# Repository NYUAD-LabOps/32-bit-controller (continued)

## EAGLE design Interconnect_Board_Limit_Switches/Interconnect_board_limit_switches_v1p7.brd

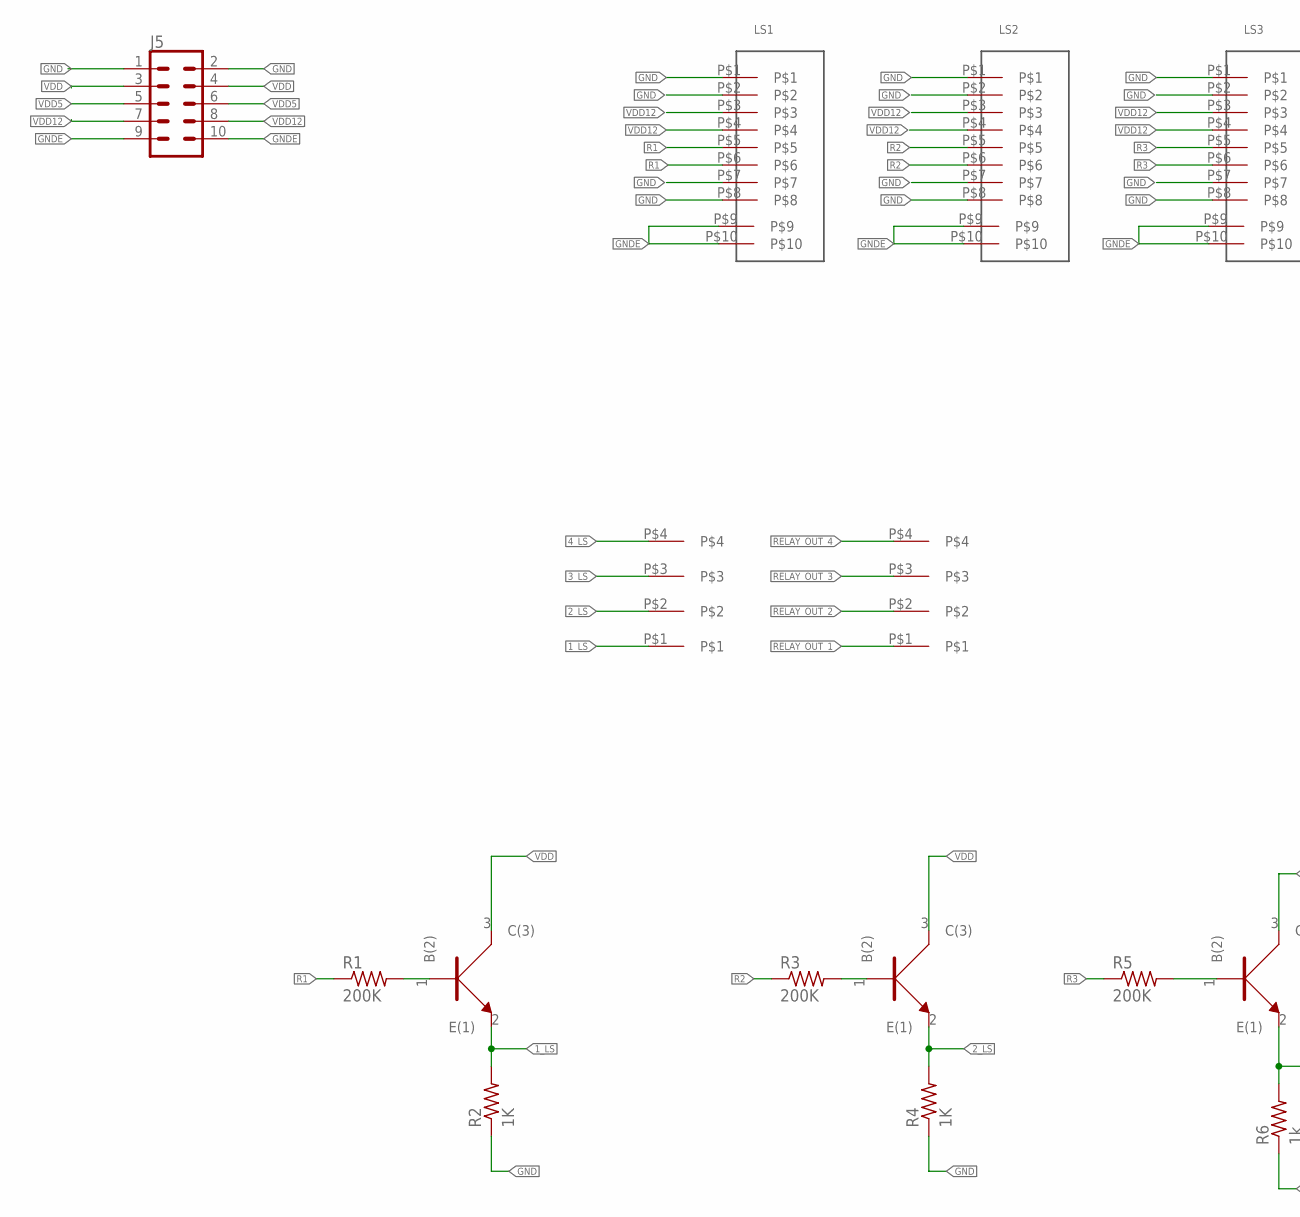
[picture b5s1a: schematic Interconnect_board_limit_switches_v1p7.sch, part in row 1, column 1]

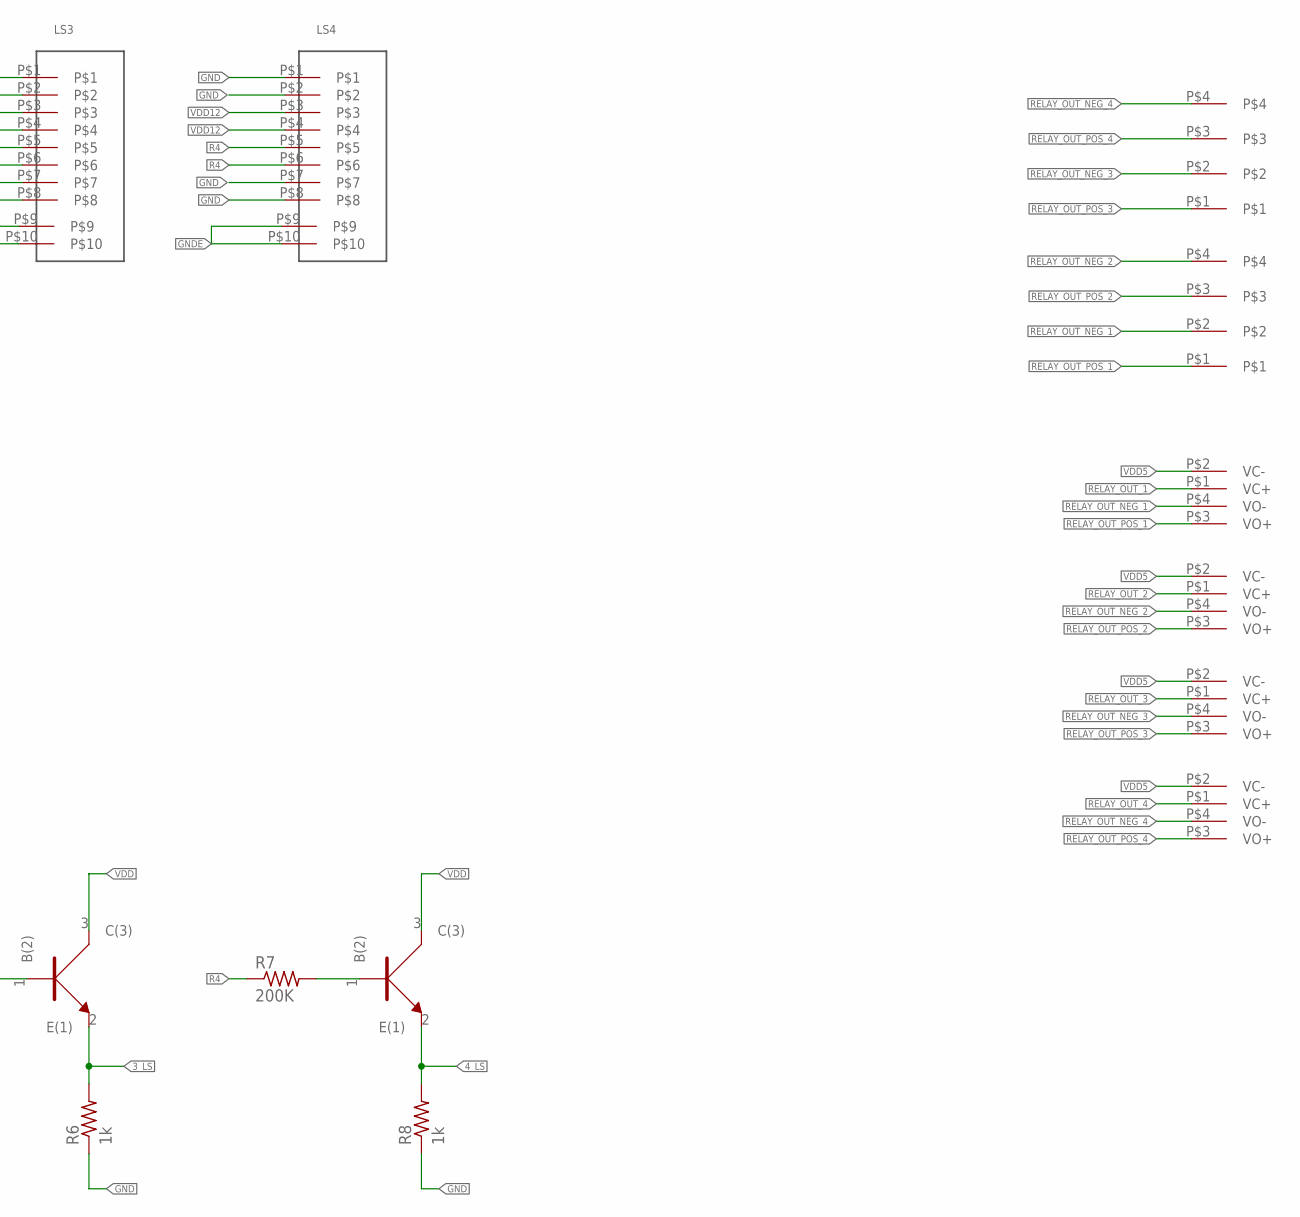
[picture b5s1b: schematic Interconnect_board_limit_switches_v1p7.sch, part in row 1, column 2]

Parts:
J1, J2, J3, J4: 3.81MM_1_X_4_RT_ANGLE_PLUG_HEADER; 1X4_3.81MM_PITCH
J5: CONN_05X2PTH; 2X5
LS1, LS2, LS3, LS4: RJ45_SMTRJ; RJ45_SMT
R1, R3, R5, R7: 200K; 0402
R2, R4: 1K; 0402
R6, R8: 1k; 0402
RELAY_1, RELAY_2, RELAY_4, RELAY_5: RELAY_KYOTO_KF0604D
U1, U2, U3, U4: BC846BW; SOT323

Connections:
1_LS: J4.P$1, R2.P$2 (2), U1.2 (E(1))
2_LS: J4.P$2, R4.P$2 (2), U2.2 (E(1))
3_LS: J4.P$3, R6.P$2 (2), U3.2 (E(1))
4_LS: J4.P$4, R8.P$2 (2), U4.2 (E(1))
GND: J5.1, J5.2, LS1.P$1, LS1.P$2, LS1.P$7, LS1.P$8, LS2.P$1, LS2.P$2, LS2.P$7, LS2.P$8, LS3.P$1, LS3.P$2, LS3.P$7, LS3.P$8, LS4.P$1, LS4.P$2, LS4.P$7, LS4.P$8, R2.P$1 (1), R4.P$1 (1), R6.P$1 (1), R8.P$1 (1)
GNDE: J5.9, J5.10, LS1.P$9, LS1.P$10, LS2.P$9, LS2.P$10, LS3.P$9, LS3.P$10, LS4.P$9, LS4.P$10
unnamed: R1.P$2 (2), U1.1 (B(2))
unnamed: R7.P$2 (2), U4.1 (B(2))
unnamed: R3.P$2 (2), U2.1 (B(2))
unnamed: R5.P$2 (2), U3.1 (B(2))
R1: LS1.P$5, LS1.P$6, R1.P$1 (1)
R2: LS2.P$5, LS2.P$6, R3.P$1 (1)
R3: LS3.P$5, LS3.P$6, R5.P$1 (1)
R4: LS4.P$5, LS4.P$6, R7.P$1 (1)
RELAY_OUT_1: J3.P$1, RELAY_1.P$1 (VC+)
RELAY_OUT_2: J3.P$2, RELAY_2.P$1 (VC+)
RELAY_OUT_3: J3.P$3, RELAY_5.P$1 (VC+)
RELAY_OUT_4: J3.P$4, RELAY_4.P$1 (VC+)
RELAY_OUT_NEG_1: J2.P$2, RELAY_1.P$4 (VO-)
RELAY_OUT_NEG_2: J2.P$4, RELAY_2.P$4 (VO-)
RELAY_OUT_NEG_3: J1.P$2, RELAY_5.P$4 (VO-)
RELAY_OUT_NEG_4: J1.P$4, RELAY_4.P$4 (VO-)
RELAY_OUT_POS_1: J2.P$1, RELAY_1.P$3 (VO+)
RELAY_OUT_POS_2: J2.P$3, RELAY_2.P$3 (VO+)
RELAY_OUT_POS_3: J1.P$1, RELAY_5.P$3 (VO+)
RELAY_OUT_POS_4: J1.P$3, RELAY_4.P$3 (VO+)
VDD: J5.3, J5.4, U1.3 (C(3)), U2.3 (C(3)), U3.3 (C(3)), U4.3 (C(3))
VDD5: J5.5, J5.6, RELAY_1.P$2 (VC-), RELAY_2.P$2 (VC-), RELAY_4.P$2 (VC-), RELAY_5.P$2 (VC-)
VDD12: J5.7, J5.8, LS1.P$3, LS1.P$4, LS2.P$3, LS2.P$4, LS3.P$3, LS3.P$4, LS4.P$3, LS4.P$4

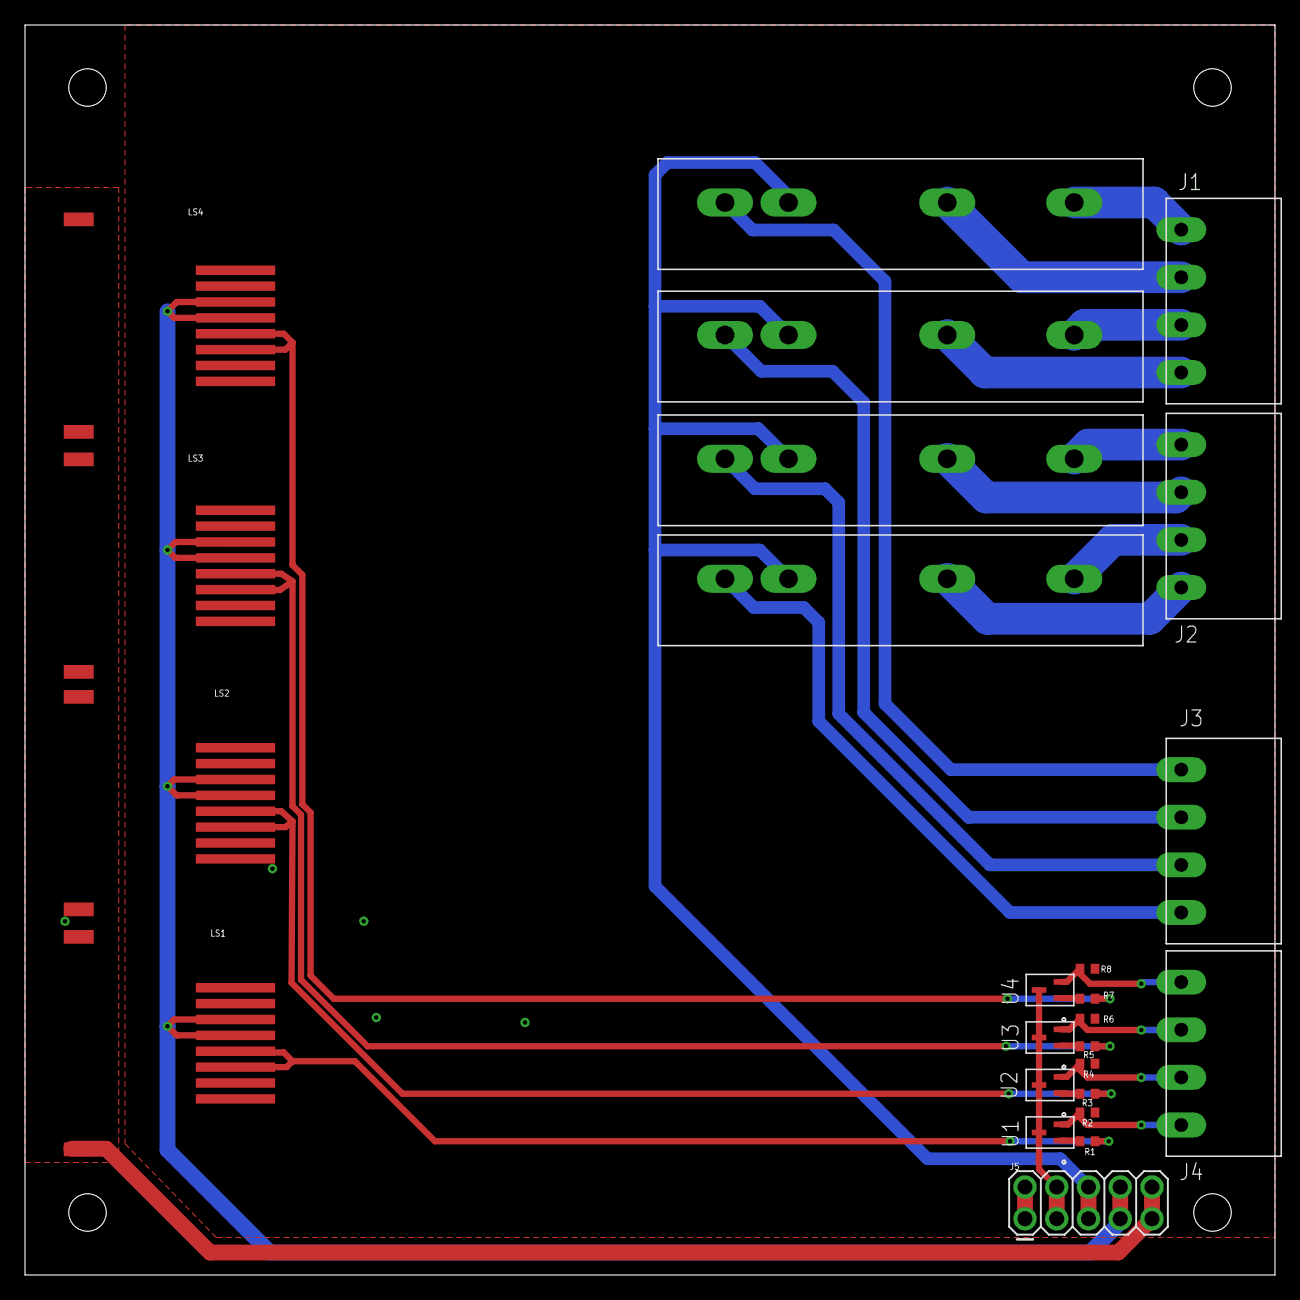
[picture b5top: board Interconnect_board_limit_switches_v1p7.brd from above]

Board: 2 copper layers, 100.0 x 100.0 mm, 25 parts (0 on the bottom side), 29 nets.

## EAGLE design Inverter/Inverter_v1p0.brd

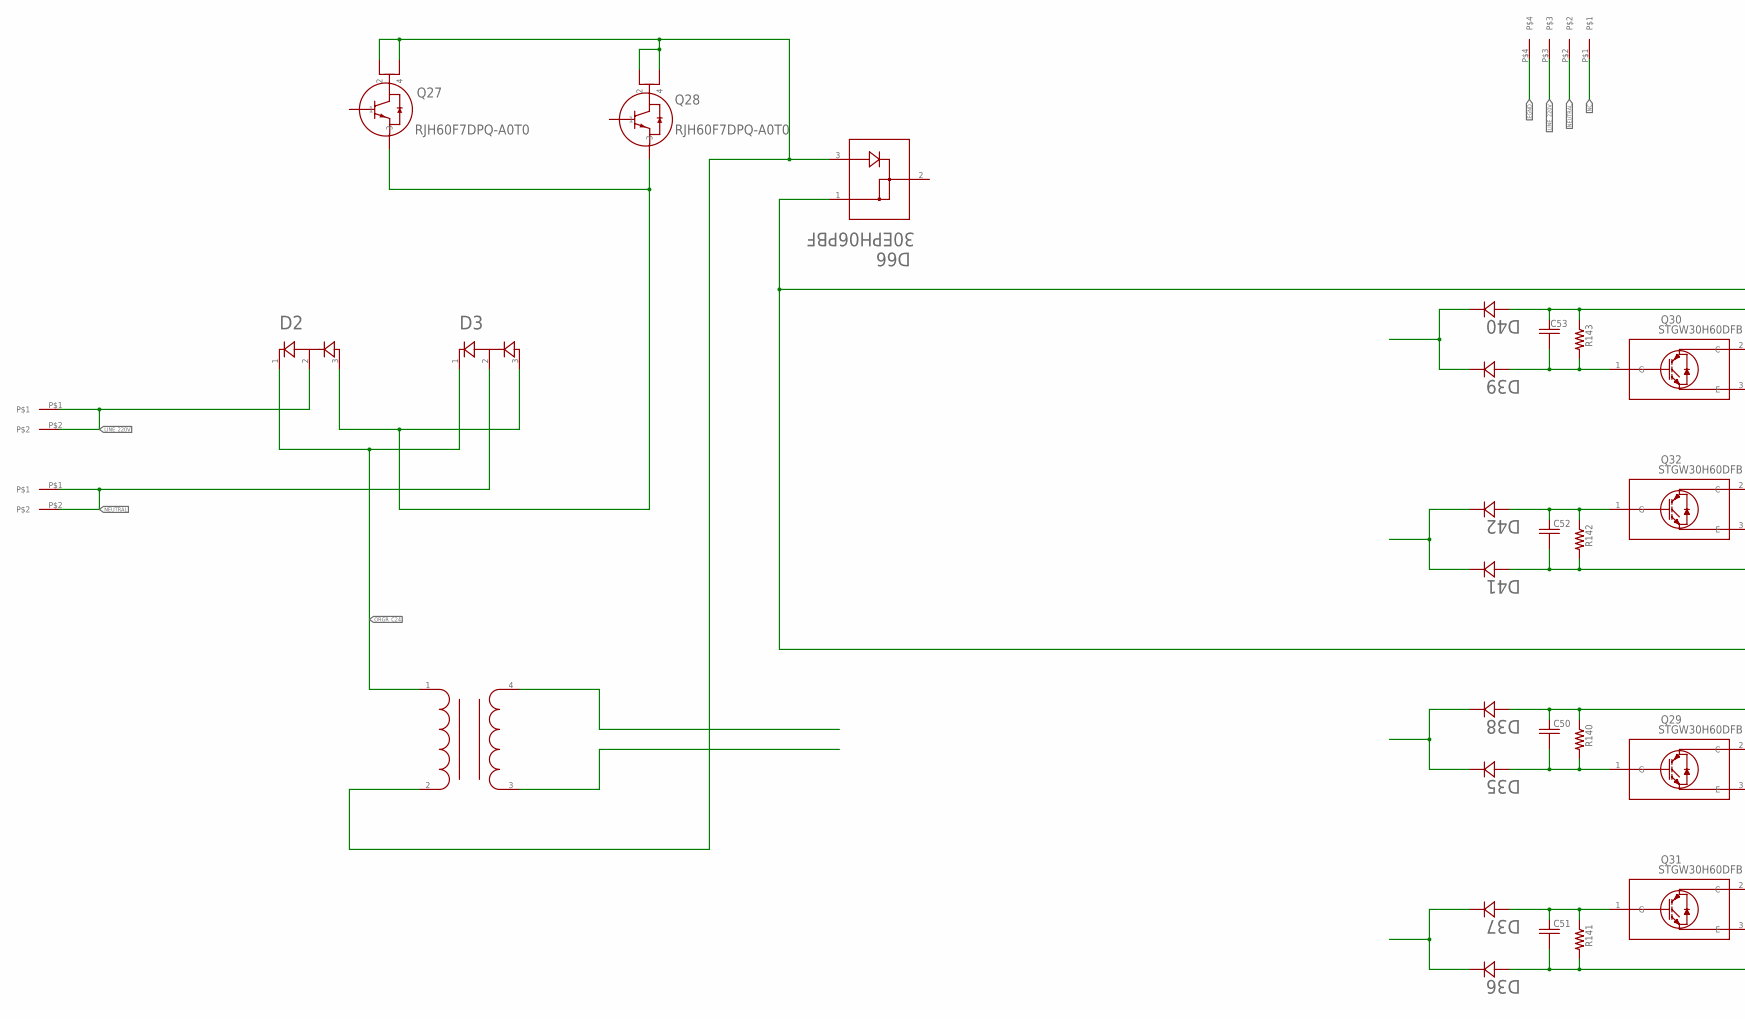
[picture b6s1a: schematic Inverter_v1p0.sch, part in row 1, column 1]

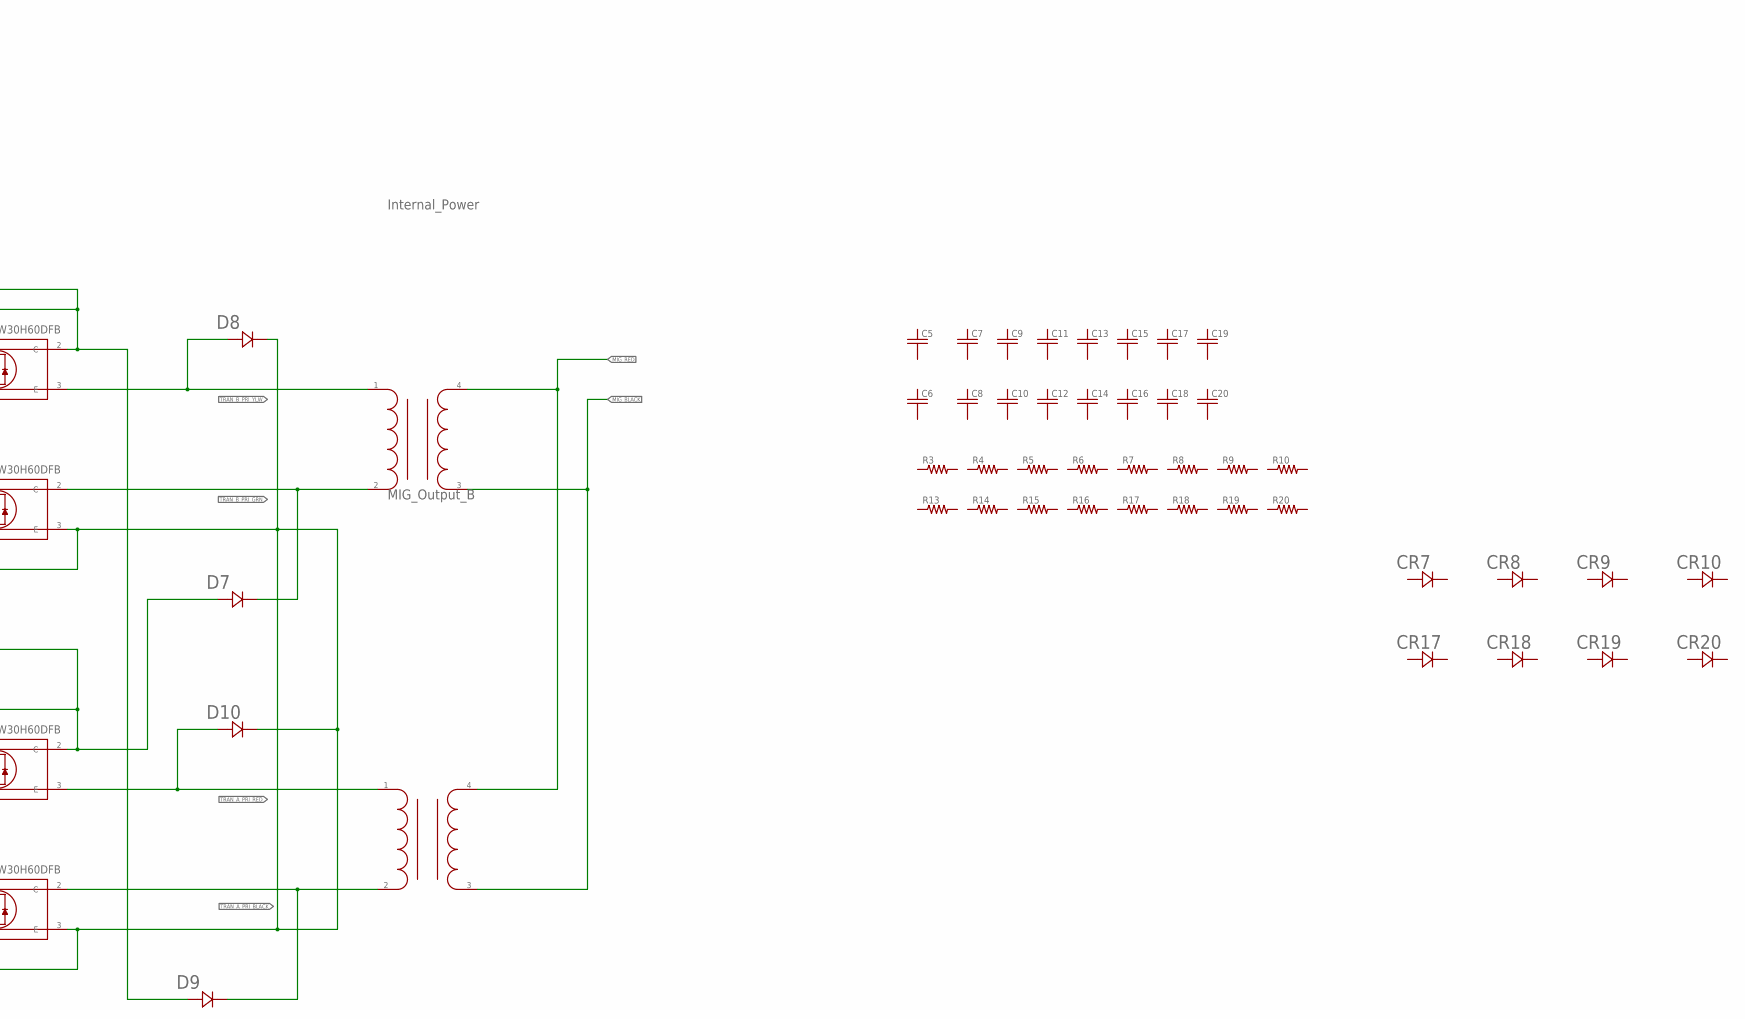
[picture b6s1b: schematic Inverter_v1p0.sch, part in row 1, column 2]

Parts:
C5, C6, C7, C8, C9, C10, C11, C12, C13, C14, C15, C16, C17, C18, C19, C20, C50, C51, C52, C53: C_0805; 0805
CR7, CR8, CR9, CR10, CR17, CR18, CR19, CR20: GF1D-E3; DO-214BA_VIS
D2, D3: SDD25N12; TO-247AD
D7, D8, D9, D10, D35, D36, D37, D38, D39, D40, D41, D42: GF1D-E3; DO-214BA_VIS
D66: 30EPH06PBF; TO-247AC_MOD_VIS
J1: 4-pos; 1X4_3.81MM_PITCH
J2, J3: 2-pos; 2_3.81MM_PITCH
Q27, Q28: RJH60F7DPQ-A0T0; TO-247A_REN
Q29, Q30, Q31, Q32: STGW30H60DFB; TO-247_STM
R3, R4, R5, R6, R7, R8, R9, R10, R13, R14, R15, R16, R17, R18, R19, R20, R140, R141, R142, R143: R_0805; 0805
U$1, U$2, U$3: GENERIC_TRANSFORMER

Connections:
EGND: J1.P$4
LINE_220V: D2.2, J1.P$3, J2.P$1, J2.P$2
MIG_BLACK: U$1.3, U$2.3
MIG_RED: U$1.4, U$2.4
unnamed: C51.1, D37.2, Q31.1 (G), R141.1
unnamed: D66.3, Q27.2, Q27.4, Q28.2, Q28.4, U$3.2
unnamed: D36.1, D37.1
unnamed: C50.2, D35.2, Q29.1 (G), R140.2
unnamed: C53.2, D39.2, Q30.1 (G), R143.2
unnamed: C50.1, C53.1, D7.2, D9.2, D38.2, D40.2, D66.1, Q29.2 (C), Q30.2 (C), R140.1, R143.1
unnamed: C52.1, D42.2, Q32.1 (G), R142.1
unnamed: C51.2, C52.2, D8.1, D10.1, D36.2, D41.2, Q31.3 (E), Q32.3 (E), R141.2, R142.2
unnamed: D41.1, D42.1
unnamed: D35.1, D38.1
unnamed: D39.1, D40.1
unnamed: D2.3, D3.3, Q27.3, Q28.3
NC: J1.P$1
NEUTRAL: D3.2, J1.P$2, J3.P$1, J3.P$2
ORGR_C24: D2.1, D3.1, U$3.1
TRAN_A_PRI_BLACK: D9.1, Q31.2 (C), U$2.2
TRAN_A_PRI_RED: D10.2, Q29.3 (E), U$2.1
TRAN_B_PRI_GRN: D7.1, Q32.2 (C), U$1.2
TRAN_B_PRI_YLW: D8.2, Q30.3 (E), U$1.1

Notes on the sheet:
MIG_Output_B
Internal_Power

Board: 2 copper layers, 75 parts (0 on the bottom side), 21 nets, no tracks yet.
